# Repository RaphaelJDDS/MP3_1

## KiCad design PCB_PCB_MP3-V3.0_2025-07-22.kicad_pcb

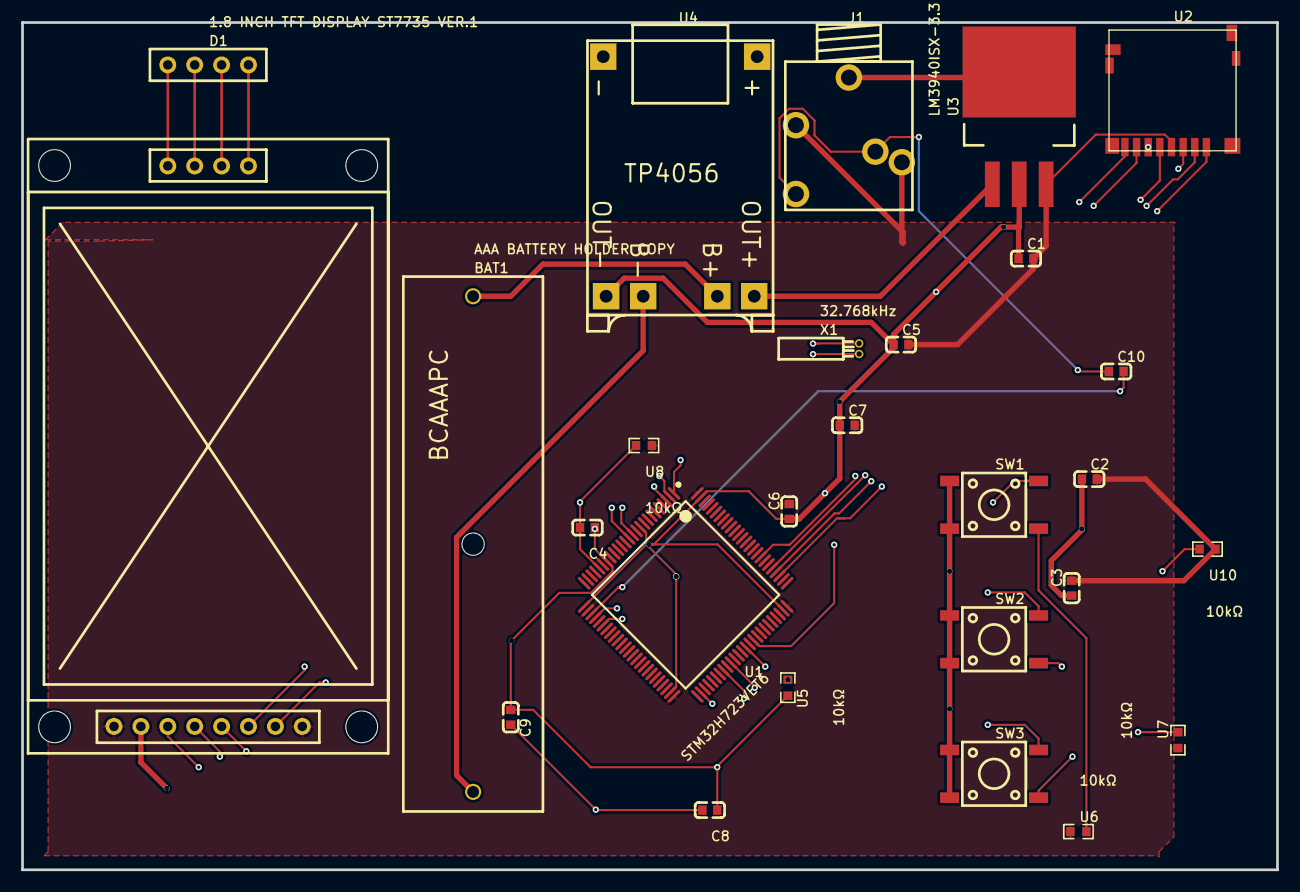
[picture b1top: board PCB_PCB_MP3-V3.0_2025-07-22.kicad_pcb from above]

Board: 4 copper layers, 118.5 x 80.0 mm, 26 parts (0 on the bottom side), 28 nets.

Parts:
BAT1: AAA BATTERY HOLDER COPY; AAA BATTERY HOLDER (BCAAAPC)
C1, C2, C3, C4, C5, C6, C7, C8, C9, C10: CAPCER0.1UF16VX5R0603,CAPCER0.1UF25VX5R0603,CAPCE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; C0603
D1: 1.8 INCH TFT DISPLAY ST7735 VER.1; 1.8_INCH_TFT_DISPLAY_ST7735
J1: Jack 3.5mm TRS female; JACK_35_ST
SW1, SW2, SW3: HX-6X6X7.3-TP FT SQUARE BUTTON; SW-SMD_4P-L6.0-W6.0-P4.50-LS9.0-H7.3
U1: STM32H723VET6; LQFP-100_L14.0-W14.0-P0.50-LS16.0-BL
U2: DM3D-MICROSDCARDCONNECTOR
U3: LM3940ISX-3.3; TO-263-3L_L10.0-W9.2-P2.54-TL
U4: TP4056 TYPE-C MODULE; TP4056 TYPE-C MODULE, 18650 1A LIPO BATTERY CHARGING BOARD
U5, U6, U7, U8, U10: 10kΩ; R0603
X1: 32.768kHz; CRYSTAL-TH_BD2.0-P0.70-D0.3

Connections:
+5V: U3.1, U4.4
ANALOG_OUT: C10.2, U1.28
B+: BAT1.1, U4.3
B-: BAT1.2, U4.2
BTN_DOWN: SW2.3, U1.2
BTN_SELECT: SW3.3, U1.3
BTN_UP: SW1.3, U1.1
CS: D1.3, U1.60
DC: D1.5, U1.64
GND: C1.1, C2.1, C3.1, C5.1, C6.1, C7.1, D1.2, J1.1, SW1.1, SW1.2, SW2.1, SW2.2, SW3.1, SW3.2, U1.10, U1.26, U1.49, U1.74, U1.99, U2.P$6, U3.2, U3.4, U4.1, U5.1
GND(ANALOG): C4.1, C8.1, C9.1, U1.19, U5.2
J1_3: C10.1, J1.3, J1.4
RES: D1.4, U1.58
SDMMC_CK: U1.80, U2.P$5
SDMMC_CMD: U1.83, U2.P$3
SDMMC_D0: U1.52, U2.P$7
SDMMC_D1: U1.66, U2.P$8
SDMMC_D2: U1.78, U2.P$1
SDMMC_D3: U1.79, U2.P$2
SPI_MOSI: D1.6, U1.31
SPI_SCK: D1.7, U1.29
SW1_4: SW1.4, U6.2
SW2_4: SW2.4, U7.2
SW3_4: SW3.4, U10.2
U1_12: U1.12, X1.2
U1_13: U1.13, X1.1
VCC: C1.2, C2.2, C3.2, C5.2, C6.2, C7.2, D1.1, D1.8, J1.2, J1.5, U1.11, U1.27, U1.50, U1.75, U1.100, U2.P$4, U3.3, U6.1, U7.1, U8.1, U10.1
VCC(ANALOG): C4.2, C8.2, C9.2, U1.21, U8.2

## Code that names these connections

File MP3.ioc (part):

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Mcu.Name=STM32H723VETx
Mcu.Package=LQFP100
Mcu.UserName=STM32H723VETx
PA13(JTMS/SWDIO).Mode=Serial_Wire
PA13(JTMS/SWDIO).Signal=DEBUG_JTMS-SWDIO
PA14(JTCK/SWCLK).Mode=Serial_Wire
PA14(JTCK/SWCLK).Signal=DEBUG_JTCK-SWCLK
PA4.Signal=COMP_DAC11_group
PA5.Mode=Full_Duplex_Master
PA5.Signal=SPI1_SCK
PA6.Mode=Full_Duplex_Master
PA6.Signal=SPI1_MISO
PA7.Mode=Full_Duplex_Master
PA7.Signal=SPI1_MOSI
PB13.Mode=SD_4_bits_Wide_bus
PB13.Signal=SDMMC1_D0
PC10.Mode=SD_4_bits_Wide_bus
PC10.Signal=SDMMC1_D2
PC11.Mode=SD_4_bits_Wide_bus
PC11.Signal=SDMMC1_D3
PC12.Mode=SD_4_bits_Wide_bus
PC12.Signal=SDMMC1_CK
PC14-OSC32_IN.Mode=LSE-External-Oscillator
PC14-OSC32_IN.Signal=RCC_OSC32_IN
PC15-OSC32_OUT.Mode=LSE-External-Oscillator
PC15-OSC32_OUT.Signal=RCC_OSC32_OUT
PC7.GPIOParameters=GPIO_Speed
PC7.GPIO_Speed=GPIO_SPEED_FREQ_HIGH
PC7.Signal=GPIO_Output
PC9.Mode=SD_4_bits_Wide_bus
PC9.Signal=SDMMC1_D1
PD11.GPIOParameters=GPIO_Speed
PD11.GPIO_Speed=GPIO_SPEED_FREQ_HIGH
PD11.Signal=GPIO_Output
PD13.GPIOParameters=GPIO_Speed
PD13.GPIO_Speed=GPIO_SPEED_FREQ_HIGH
PD13.Signal=GPIO_Output
PD2.Mode=SD_4_bits_Wide_bus
PD2.Signal=SDMMC1_CMD
PE2.GPIOParameters=GPIO_PuPd,GPIO_Label
PE2.GPIO_Label=BTN_UP
PE2.GPIO_PuPd=GPIO_PULLUP
PE2.Signal=GPIO_Input
PE3.GPIOParameters=GPIO_PuPd,GPIO_Label
PE3.GPIO_Label=BTN_DOWN
PE3.GPIO_PuPd=GPIO_PULLUP
PE3.Signal=GPIO_Input
PE4.GPIOParameters=GPIO_PuPd,GPIO_Label
PE4.GPIO_Label=BTN_SELECT
PE4.GPIO_PuPd=GPIO_PULLUP
PE4.Signal=GPIO_Input
RCC.HSE_VALUE=32768000
RCC.SYSCLKFreq_VALUE=320000000
RCC.SYSCLKSource=RCC_SYSCLKSOURCE_PLLCLK
board=custom

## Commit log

2025-08-03 Add files via upload
    Link: https://cad.onshape.com/documents/b537c34aeda43478a77d1f9e/w/4093028cf3bff62ce3654597/e/53506afbc5e0a3e98832b060?renderMode=0&uiState=688ece3711094d0a21e597af
2025-08-03 STM32 project code
